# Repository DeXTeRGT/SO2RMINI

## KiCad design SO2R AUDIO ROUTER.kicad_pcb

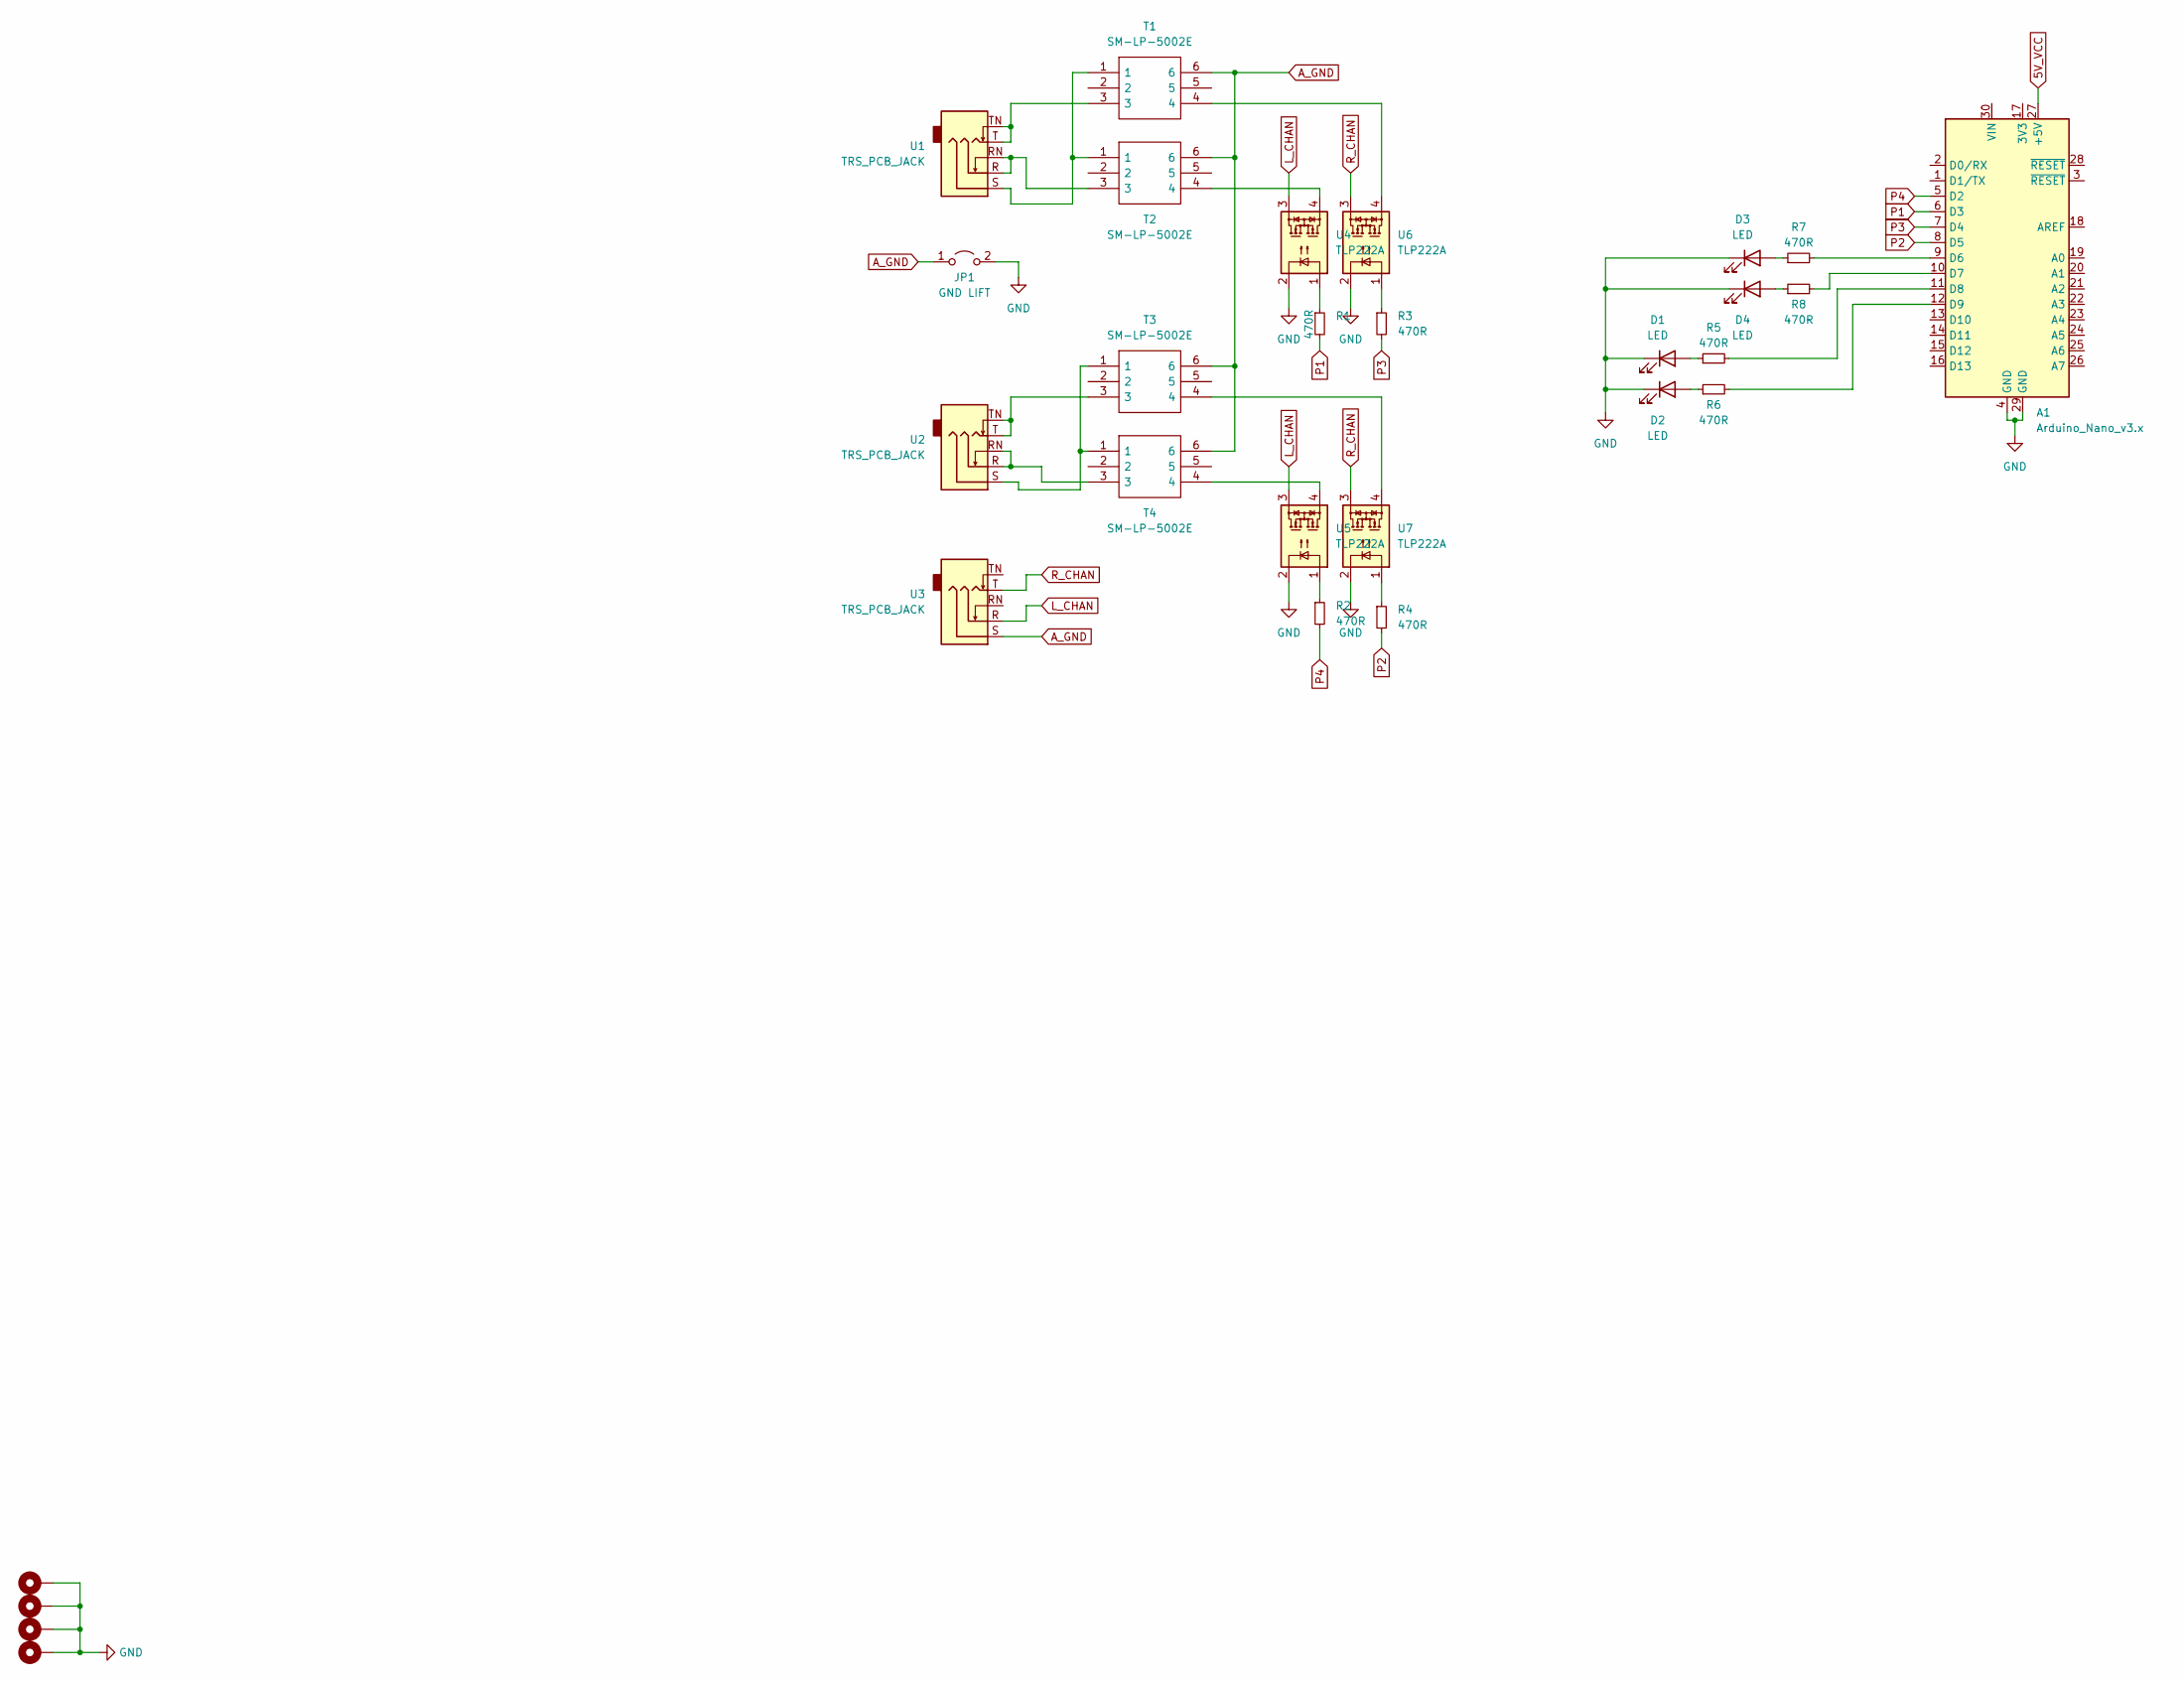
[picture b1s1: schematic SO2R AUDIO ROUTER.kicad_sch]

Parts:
A1: Arduino_Nano_v3.x; Arduino_Nano
D1, D2, D3, D4: LED; LED_D3.0mm_Horizontal_O3.81mm_Z2.0mm
H1, H2, H3, H4: MountingHole_Pad; MountingHole_3.5mm_Pad_Via
JP1: GND LIFT; PinHeader_1x02_P2.54mm_Vertical
R1, R2, R3, R4, R5, R6, R7, R8: 470R; R_0805_2012Metric_Pad1.20x1.40mm_HandSolder
T1, T2, T3, T4: SM-LP-5002E; SMLP5002E
U1, U2, U3: TRS_PCB_JACK; STEREO_3.5MM_PCB
U4, U5, U6, U7: TLP222A; SO-4_4.4x4.3mm_P2.54mm

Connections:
5V_VCC: A1.27 (+5V)
A_GND: JP1.1 (A), T1.6, T2.6, T3.6, T4.6, U3.S
GND: A1.4 (GND), A1.29 (GND), D1.1 (K), D2.1 (K), D3.1 (K), D4.1 (K), H1.1, H2.1, H3.1, H4.1, JP1.2 (B), U4.2, U5.2, U6.2, U7.2
L_CHAN: U3.R, U4.3, U5.3
unnamed: A1.9 (D6), R7.2
unnamed: A1.10 (D7), R8.2
unnamed: A1.11 (D8), R5.2
unnamed: A1.12 (D9), R6.2
unnamed: D1.2 (A), R5.1
unnamed: D2.2 (A), R6.1
unnamed: D3.2 (A), R7.1
unnamed: D4.2 (A), R8.1
unnamed: R1.1, U4.1
unnamed: R2.1, U5.1
unnamed: R3.1, U6.1
unnamed: R4.1, U7.1
unnamed: T1.1, T2.1, U1.S
unnamed: T1.3, U1.T, U1.TN
unnamed: T1.4, U6.4
unnamed: T2.3, U1.R, U1.RN
unnamed: T2.4, U4.4
unnamed: T3.1, T4.1, U2.S
unnamed: T3.3, U2.T, U2.TN
unnamed: T3.4, U7.4
unnamed: T4.3, U2.R, U2.RN
unnamed: T4.4, U5.4
P1: A1.6 (D3), R1.2
P2: A1.8 (D5), R4.2
P3: A1.7 (D4), R3.2
P4: A1.5 (D2), R2.2
R_CHAN: U3.T, U6.3, U7.3

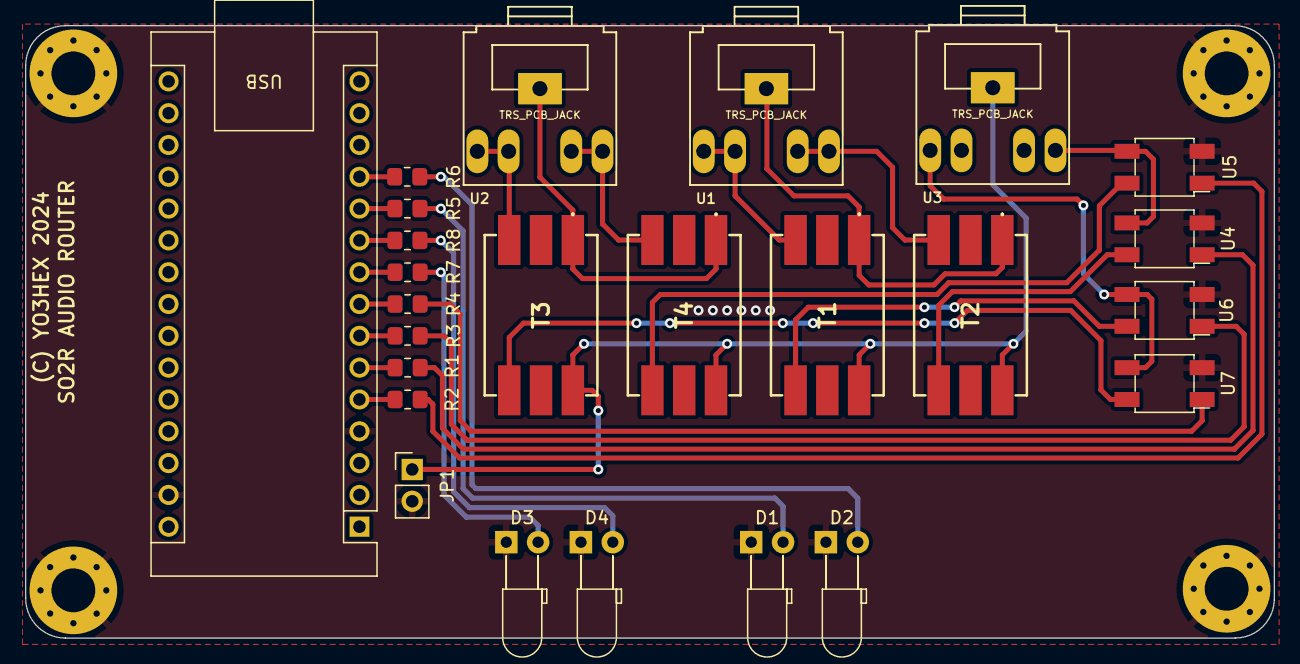
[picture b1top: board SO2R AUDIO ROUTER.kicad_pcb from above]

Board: 2 copper layers, 99.7 x 48.9 mm, 29 parts (0 on the bottom side), 30 nets.
